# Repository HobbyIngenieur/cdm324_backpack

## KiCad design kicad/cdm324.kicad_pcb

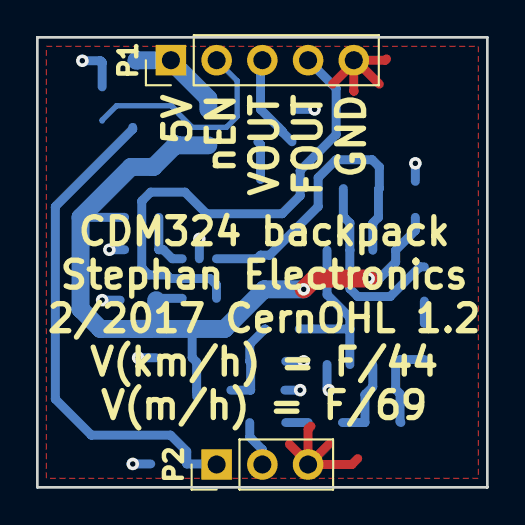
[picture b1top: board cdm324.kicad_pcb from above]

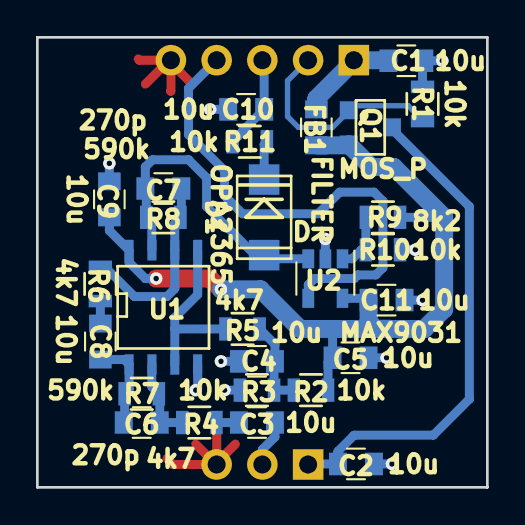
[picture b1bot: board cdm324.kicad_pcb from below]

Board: 2 copper layers, 25.0 x 25.0 mm, 29 parts (27 on the bottom side), 18 nets.

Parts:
C1, C2, C3, C4, C5, C8, C9, C10, C11: 10u; C_0805
C6, C7: 270p; C_0805
D1: D; DIODE_SMA
FB1: FILTER; C_0805
P1: CONN_01X05; Pin_Header_Straight_1x05_Pitch2.54mm
P2: CONN_01X03; Pin_Header_Straight_1x03_Pitch2.54mm
Q1: MOS_P; SOT23-3
R1, R2, R3, R10, R11: 10k; R_0805
R4, R5, R6: 4k7; R_0805
R7, R8: 590k; R_0805
R9: 8k2; R_0805
U1: OPA2365; SOIC-8-N
U2: MAX9031; SOT-23-5

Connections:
+5V: C1.1, FB1.1, P1.1
/FOUT: P1.4, U2.4
/VOUT: C10.1, P1.3, R11.2
/nEN: P1.2, Q1.1, R1.1
GND: C1.2, C2.2, C4.2, C5.2, C9.2, C10.2, C11.2, P1.5, P2.3, R1.2, R3.2, R10.2, U1.4, U2.2
unnamed: C2.1, P2.1, Q1.3
unnamed: C3.1, P2.2
unnamed: C3.2, R4.1
unnamed: C4.1, R2.2, R3.1, R5.1
unnamed: C6.1, R4.2, R7.1, U1.2
unnamed: C6.2, C8.2, R7.2, U1.1
unnamed: C7.1, R6.1, R8.2, U1.6
unnamed: C7.2, D1.2, R8.1, U1.7, U2.3
unnamed: C8.1, R6.2
unnamed: C5.1, C9.1, C11.1, FB1.2, Q1.2, R2.1, R9.1, U1.8, U2.5
unnamed: D1.1, R11.1
unnamed: R5.2, U1.3, U1.5
unnamed: R9.2, R10.1, U2.1

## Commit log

2020-01-22 preparations for mechanical changes made
